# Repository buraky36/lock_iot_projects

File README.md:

# lock_iot_projects
Barfas Projects

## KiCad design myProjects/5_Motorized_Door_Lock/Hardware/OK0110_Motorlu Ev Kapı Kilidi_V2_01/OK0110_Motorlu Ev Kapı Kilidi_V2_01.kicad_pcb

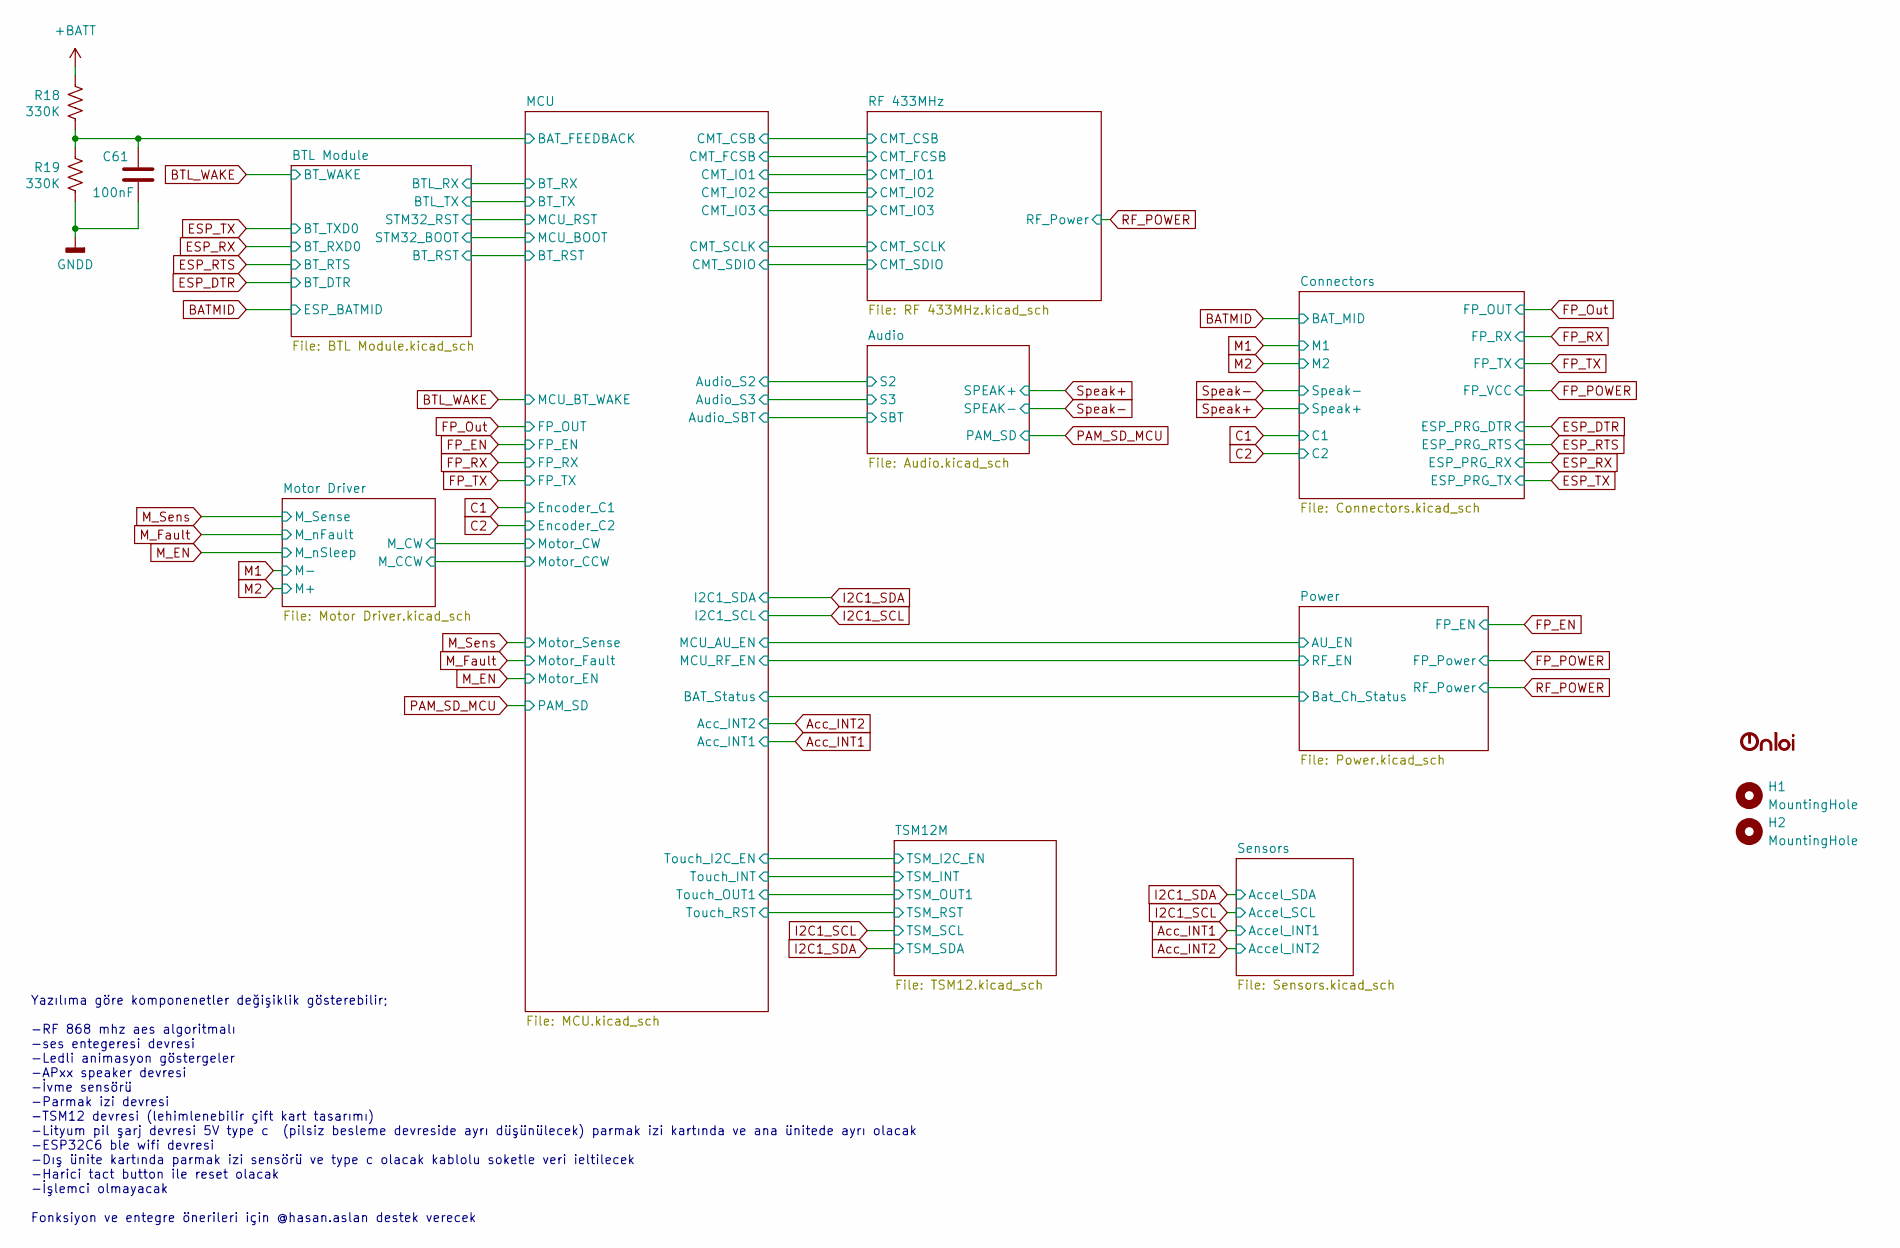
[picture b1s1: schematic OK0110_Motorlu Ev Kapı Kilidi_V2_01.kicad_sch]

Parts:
C61: 100nF; C_0402_1005Metric
H1, H2: MountingHole; MountingHole_4.3mm_M4
LOGO1: ONLOI_7_5x2_5mm
R18, R19: 330K; R_0402_1005Metric

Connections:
+BATT: R18.2; also elsewhere on the board
/MCU/BAT_FEEDBACK: C61.2, R18.1, R19.2; also elsewhere on the board
GNDD: C61.1, R19.1; also elsewhere on the board

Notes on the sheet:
Yazılıma göre komponenetler değişiklik gösterebilir; -RF 868 mhz aes algoritmalı -ses entegeresi devresi -Ledli animasyon göstergeler -APxx speaker devresi -İvme sensörü -Parmak izi devresi -TSM12 devresi (lehimlenebilir çift kart tasarımı) -Lityum pil şarj devresi 5V type c (pilsiz besleme devresi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

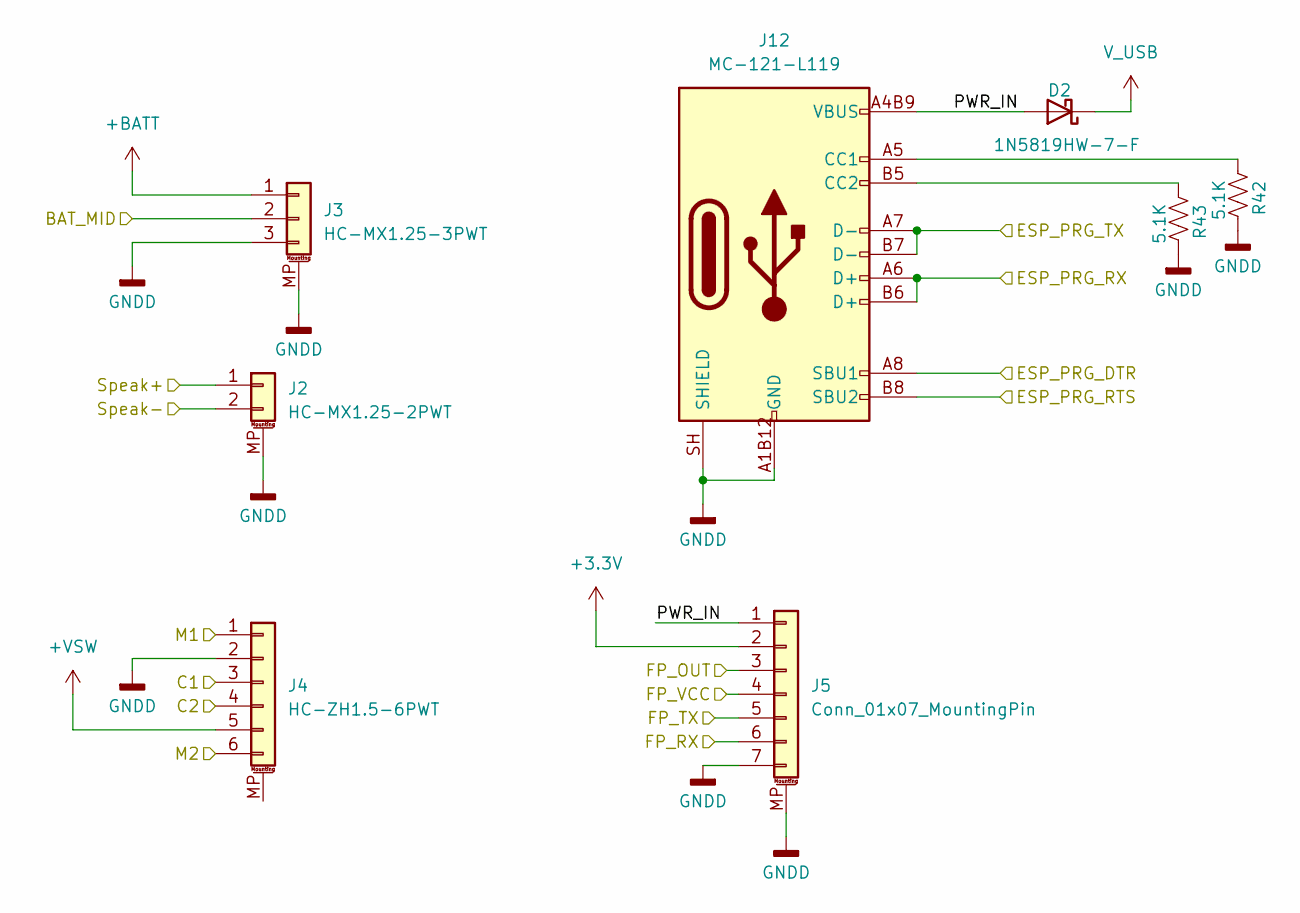
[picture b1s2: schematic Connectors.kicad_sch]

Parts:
D2: 1N5819HW-7-F; D_SOD-110
J2: HC-MX1.25-2PWT; JST_GH_SM02B-GHS-TB_1x02-1MP_P1.25mm_Horizontal
J3: HC-MX1.25-3PWT; JST_GH_SM03B-GHS-TB_1x03-1MP_P1.25mm_Horizontal
J4: HC-ZH1.5-6PWT; JST_ZE_SM06B-ZESS-TB_1x06-1MP_P1.50mm_Horizontal
J5: Conn_01x07_MountingPin; JST_SHL_SM07B-SHLS-TF_1x07-1MP_P1.00mm_Horizontal
J12: MC-121-L119; USB_C_Receptacle_GCT_USB4105-xx-A_16P_TopMnt_Horizontal
R42, R43: 5.1K; R_0402_1005Metric

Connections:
+3.3V: J5.2; also elsewhere on the board
+BATT: J3.1; also elsewhere on the board
+VSW: J4.5; also elsewhere on the board
/Connectors/PWR_IN: D2.2 (A), J5.1, J12.A4B9 (VBUS), J12.B4A9 (VBUS)
BATMID: J3.2; also elsewhere on the board
C1: J4.3; also elsewhere on the board
C2: J4.4; also elsewhere on the board
ESP_DTR: J12.A8 (SBU1); also elsewhere on the board
ESP_RTS: J12.B8 (SBU2); also elsewhere on the board
ESP_RX: J12.A6 (D+), J12.B6 (D+); also elsewhere on the board
ESP_TX: J12.A7 (D-), J12.B7 (D-); also elsewhere on the board
FP_Out: J5.3; also elsewhere on the board
FP_POWER: J5.4; also elsewhere on the board
FP_RX: J5.6; also elsewhere on the board
FP_TX: J5.5; also elsewhere on the board
GNDD: J2.MP (MountPin), J3.3, J3.MP (MountPin), J4.2, J5.7, J5.MP (MountPin), J12.A1B12 (GND), J12.B1A12 (GND), J12.SH (SHIELD), R42.2, R43.2; also elsewhere on the board
M1: J4.1; also elsewhere on the board
M2: J4.6; also elsewhere on the board
unnamed: J12.A5 (CC1), R42.1
unnamed: J12.B5 (CC2), R43.1
Speak+: J2.1; also elsewhere on the board
Speak-: J2.2; also elsewhere on the board
V_USB: D2.1 (K); also elsewhere on the board

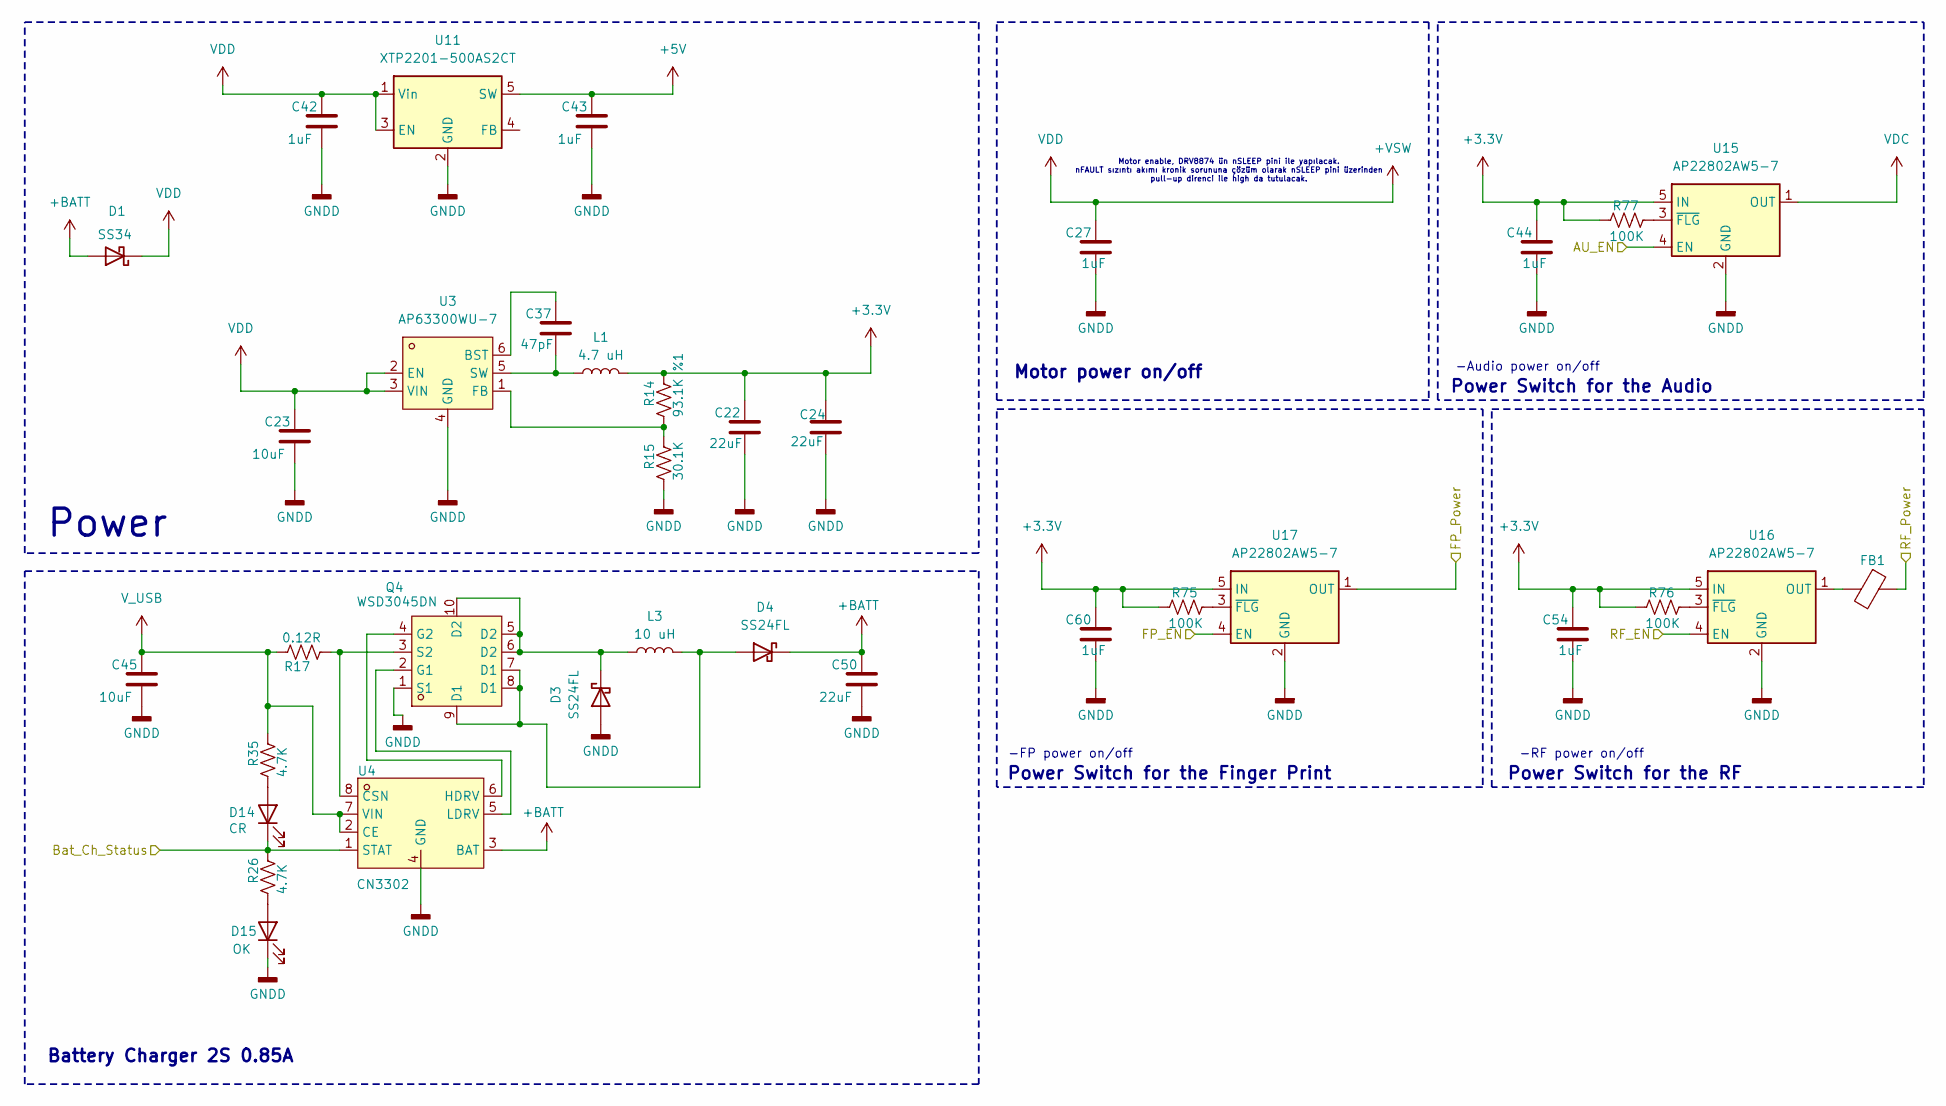
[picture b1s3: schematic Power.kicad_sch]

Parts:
C22, C24, C50: 22uF; C_0603_1608Metric
C23: 10uF; C_0402_1005Metric
C27, C42, C43, C44, C54, C60: 1uF; C_0402_1005Metric
C37: 47pF; C_0402_1005Metric
C45: 10uF; C_0603_1608Metric
D1: SS34; D_SMA
D3, D4: SS24FL; D_SOD-123F; MPN SS24FL
D14: CR; LED_0603_1608Metric
D15: OK; LED_0603_1608Metric
FB1: L_0805_2012Metric
L1: 4.7 uH; L_1008_2520Metric
L3: 10 uH; L_Cenker_CKCS6045
Q4: WSD3045DN; DFN-8_L3.2-W3.2-P0.65-LS3.4-BL-EP; MPN WSD3045DN33; LCSC Part C377868
R14: 93.1K %1; R_0402_1005Metric
R15: 30.1K; R_0402_1005Metric
R17: 0.12R; R_0603_1608Metric
R26, R35: 4.7K; R_0402_1005Metric
R75, R76, R77: 100K; R_0402_1005Metric
U3: AP63300WU-7; TSOT-23-6_L2.9-W1.6-P0.95-LS2.8-BR; MPN AP63300WU-7; LCSC Part C2158012
U4: CN3302; SOP-8_L4.9-W3.9-P1.27-LS6.0-BL; MPN CN3302; LCSC Part C559039
U11: XTP2201-500AS2CT; TSOT-23-5
U15, U16, U17: AP22802AW5-7; SOT-23-5

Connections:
+3.3V: C22.2, C24.1, C44.2, C54.2, C60.2, L1.2, R14.1, R75.1, R76.1, R77.1, U15.5 (IN), U16.5 (IN), U17.5 (IN); also elsewhere on the board
+5V: C43.2, U11.5 (SW); also elsewhere on the board
+BATT: C50.2, D1.2 (A), D4.1 (K), U4.3 (BAT); also elsewhere on the board
+VSW: C23.2, C27.2, C42.2, D1.1 (K), U3.2 (EN), U3.3 (VIN), U11.1 (Vin), U11.3 (EN); also elsewhere on the board
/MCU/BAT_Status: D14.1 (K), R26.1, U4.1 (STAT); also elsewhere on the board
/MCU/MCU_AU_EN: U15.4 (EN); also elsewhere on the board
/MCU/MCU_RF_EN: U16.4 (EN); also elsewhere on the board
FP_EN: U17.4 (EN); also elsewhere on the board
FP_POWER: U17.1 (OUT); also elsewhere on the board
GNDD: C22.1, C23.1, C24.2, C27.1, C42.1, C43.1, C44.1, C45.1, C50.1, C54.1, C60.1, D3.2 (A), D15.1 (K), Q4.1 (S1), R15.2, U3.4 (GND), U4.4 (GND), U11.2 (GND), U15.2 (GND), U16.2 (GND), U17.2 (GND); also elsewhere on the board
unnamed: D3.1 (K), L3.1, Q4.5 (D2), Q4.6 (D2), Q4.10 (D2)
unnamed: D4.2 (A), L3.2, Q4.7 (D1), Q4.8 (D1), Q4.9 (D1)
unnamed: D14.2 (A), R35.2
unnamed: D15.2 (A), R26.2
unnamed: Q4.2 (G1), U4.5 (LDRV)
unnamed: Q4.4 (G2), U4.6 (HDRV)
unnamed: Q4.3 (S2), R17.2, U4.8 (CSN)
unnamed: C37.2, U3.6 (BST)
unnamed: R14.2, R15.1, U3.1 (FB)
unnamed: C37.1, L1.1, U3.5 (SW)
unnamed: R77.2, U15.3 (~FLG)
unnamed: FB1.2, U16.1 (OUT)
unnamed: R76.2, U16.3 (~FLG)
unnamed: R75.2, U17.3 (~FLG)
RF_POWER: FB1.1; also elsewhere on the board
VDC: U15.1 (OUT); also elsewhere on the board
V_USB: C45.2, R17.1, R35.1, U4.2 (CE), U4.7 (VIN); also elsewhere on the board

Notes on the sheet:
-Audio power on/off
-RF power on/off
Battery Charger 2S 0.85A
Power Switch for the RF
Motor power on/off
Motor enable, DRV8874 ün nSLEEP pini ile yapılacak. nFAULT sızıntı akımı kronik sorununa çözüm olarak nSLEEP pini üzerinden pull-up direnci ile high da tutulacak.
Power Switch for the Audio
Power
Power Switch for the Finger Print
-FP power on/off

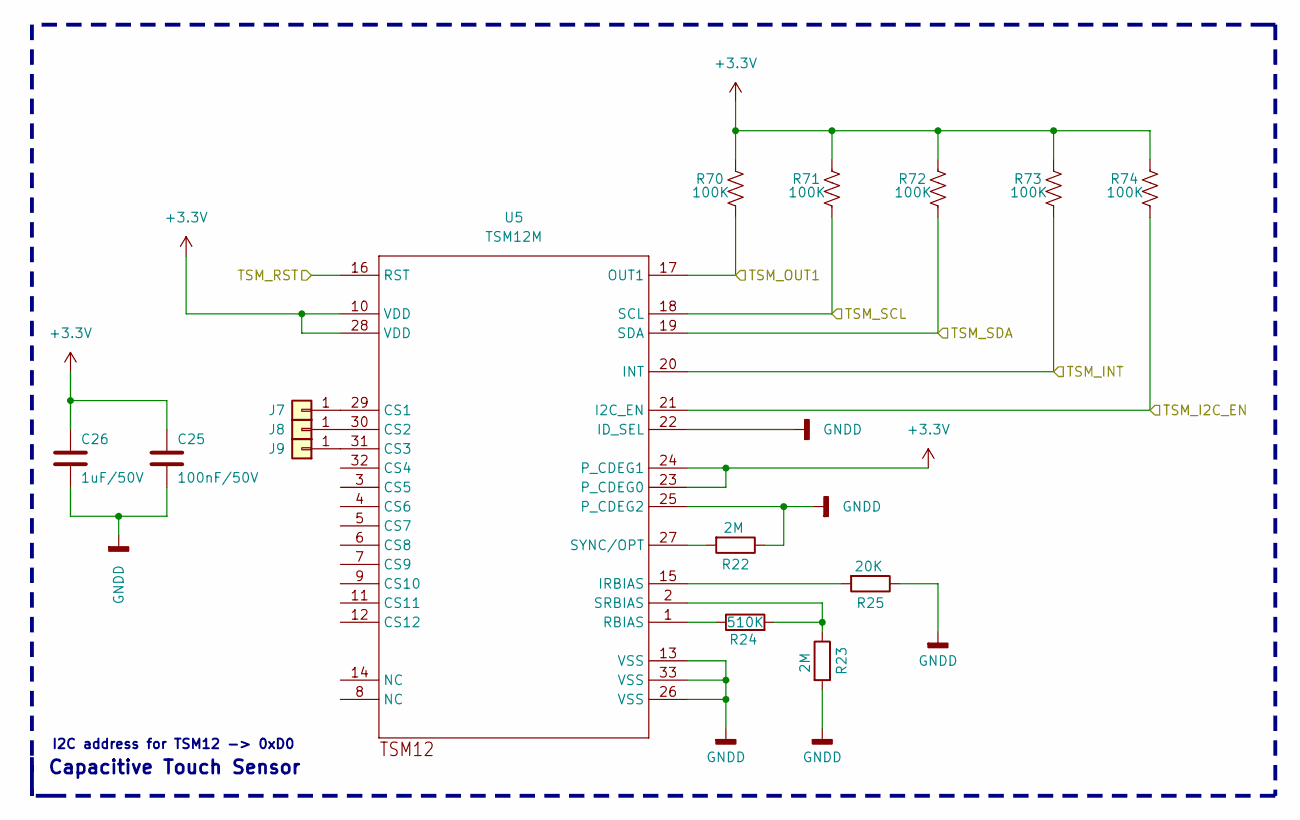
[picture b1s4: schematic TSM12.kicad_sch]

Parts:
C25: 100nF/50V; C_0402_1005Metric
C26: 1uF/50V; C_0402_1005Metric
J7, J8, J9: TestPoint:TestPoint_Keystone_5015_Micro_Mini; TestPoint_Keystone_5015_Micro_Mini
R22, R23: 2M; R_0402_1005Metric
R24: 510K; R_0402_1005Metric
R25: 20K; R_0402_1005Metric
R70, R71, R72, R73, R74: 100K; R_0402_1005Metric
U5: TSM12M; QFN-32-1EP_5x5mm_P0.5mm_EP3.1x3.1mm_ThermalVias

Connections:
+3.3V: C25.1, C26.1, R70.1, R71.1, R72.1, R73.1, R74.1, U5.10 (VDD), U5.23 (P_CDEG0), U5.24 (P_CDEG1), U5.28 (VDD); also elsewhere on the board
/MCU/Touch_I2C_EN: R74.2, U5.21 (I2C_EN); also elsewhere on the board
/MCU/Touch_INT: R73.2, U5.20 (INT); also elsewhere on the board
/MCU/Touch_OUT1: R70.2, U5.17 (OUT1); also elsewhere on the board
/MCU/Touch_RST: U5.16 (RST); also elsewhere on the board
GNDD: C25.2, C26.2, R22.1, R23.2, R25.1, U5.13 (VSS), U5.22 (ID_SEL), U5.25 (P_CDEG2), U5.26 (VSS), U5.33 (VSS); also elsewhere on the board
I2C1_SCL: R71.2, U5.18 (SCL); also elsewhere on the board
I2C1_SDA: R72.2, U5.19 (SDA); also elsewhere on the board
unnamed: J7.1 (Pin_1_1), U5.29 (CS1)
unnamed: J8.1 (Pin_1_1), U5.30 (CS2)
unnamed: J9.1 (Pin_1_1), U5.31 (CS3)
unnamed: R25.2, U5.15 (IRBIAS)
unnamed: R24.1, U5.1 (RBIAS)
unnamed: R23.1, R24.2, U5.2 (SRBIAS)
unnamed: R22.2, U5.27 (SYNC/OPT)

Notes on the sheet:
I2C address for TSM12 -> 0xD0
Capacitive Touch Sensor

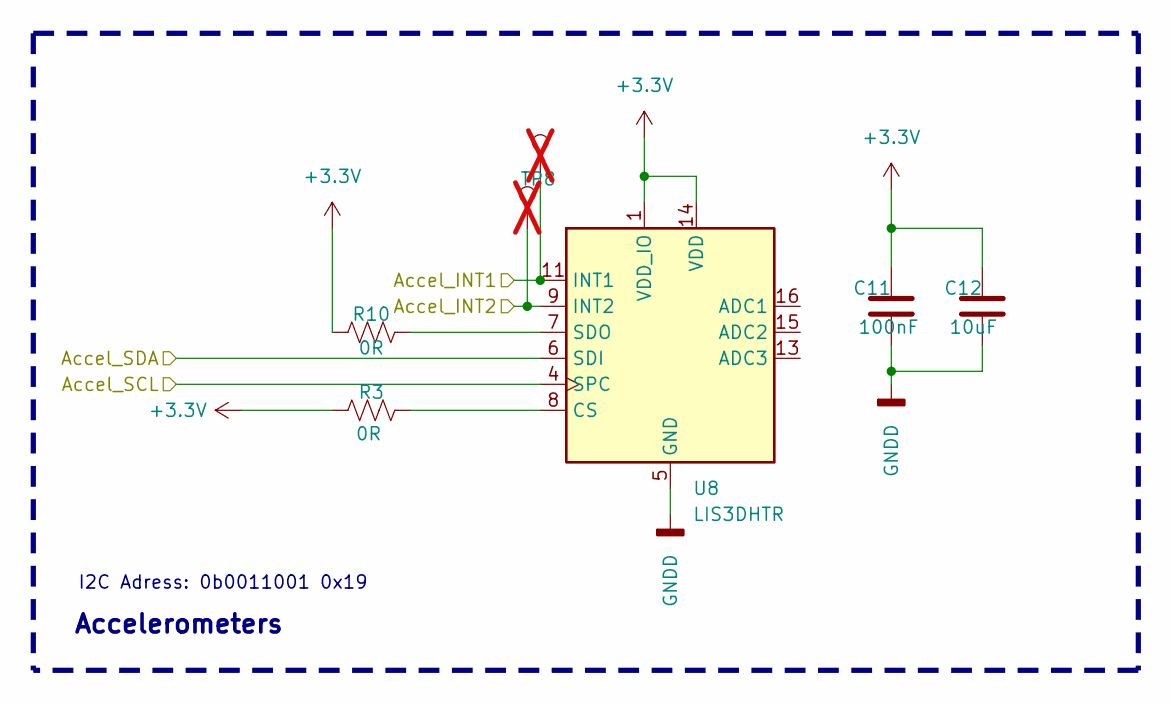
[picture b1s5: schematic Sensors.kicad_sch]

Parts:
C11: 100nF; C_0402_1005Metric
C12: 10uF; C_0402_1005Metric
R3, R10: 0R; R_0402_1005Metric
TP7, TP8: TestPoint; TestPoint_Pad_D1.0mm; not fitted
U8: LIS3DHTR; LGA-16_3x3mm_P0.5mm_LayoutBorder3x5y

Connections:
+3.3V: C11.1, C12.1, R3.1, R10.1, U8.1 (VDD_IO), U8.14 (VDD); also elsewhere on the board
Acc_INT1: TP7.1, U8.11 (INT1); also elsewhere on the board
Acc_INT2: TP8.1, U8.9 (INT2); also elsewhere on the board
GNDD: C11.2, C12.2, U8.5 (GND), U8.10 (GND), U8.12 (GND); also elsewhere on the board
I2C1_SCL: U8.4 (SPC); also elsewhere on the board
I2C1_SDA: U8.6 (SDI); also elsewhere on the board
unnamed: R3.2, U8.8 (CS)
unnamed: R10.2, U8.7 (SDO)

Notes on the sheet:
Accelerometers
I2C Adress: 0b0011001 0x19

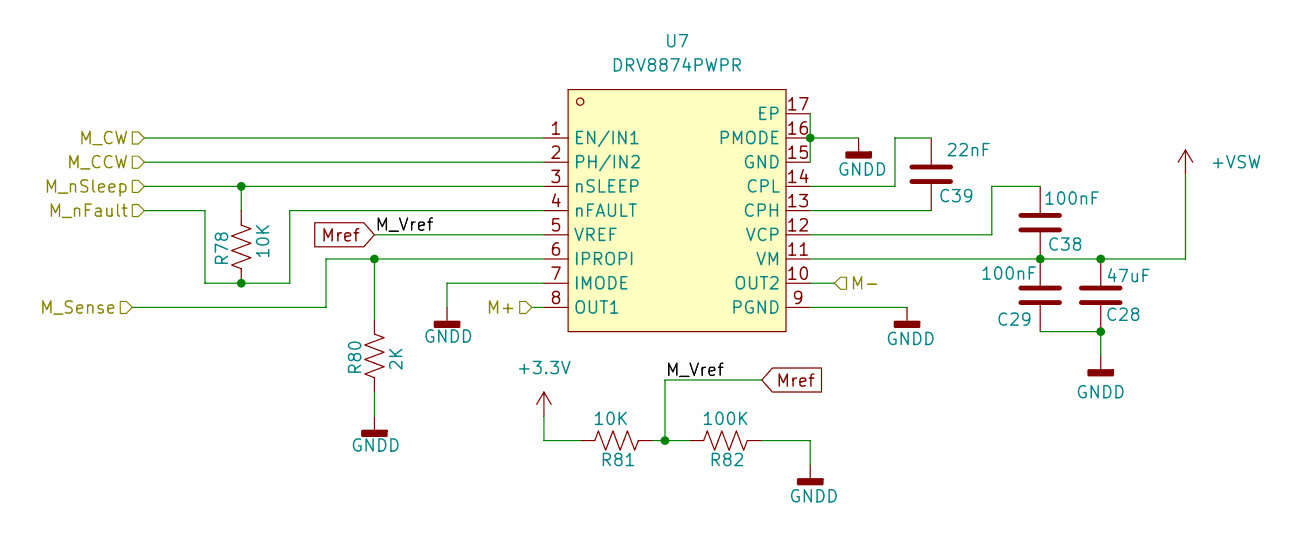
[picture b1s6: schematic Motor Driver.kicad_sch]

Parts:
C28: 47uF; C_1206_3216Metric
C29, C38: 100nF; C_0402_1005Metric
C39: 22nF; C_0402_1005Metric
R78, R81: 10K; R_0402_1005Metric
R80: 2K; R_0402_1005Metric
R82: 100K; R_0402_1005Metric
U7: DRV8874PWPR; HTSSOP-16_L5.0-W4.4-P0.65-LS6.4-BL-EP; MPN DRV8874PWPR; LCSC Part C1855818

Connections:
+3.3V: R81.2; also elsewhere on the board
+VSW: C28.2, C29.2, C38.1, U7.11 (VM); also elsewhere on the board
/MCU/Motor_CCW: U7.2 (PH/IN2); also elsewhere on the board
/MCU/Motor_CW: U7.1 (EN/IN1); also elsewhere on the board
GNDD: C28.1, C29.1, R80.1, R82.1, U7.7 (IMODE), U7.9 (PGND), U7.15 (GND), U7.16 (PMODE), U7.17 (EP); also elsewhere on the board
M1: U7.10 (OUT2); also elsewhere on the board
M2: U7.8 (OUT1); also elsewhere on the board
M_EN: R78.2, U7.3 (nSLEEP); also elsewhere on the board
M_Fault: R78.1, U7.4 (nFAULT); also elsewhere on the board
M_Sens: R80.2, U7.6 (IPROPI); also elsewhere on the board
Mref: R81.1, R82.2, U7.5 (VREF)
unnamed: C39.1, U7.13 (CPH)
unnamed: C39.2, U7.14 (CPL)
unnamed: C38.2, U7.12 (VCP)

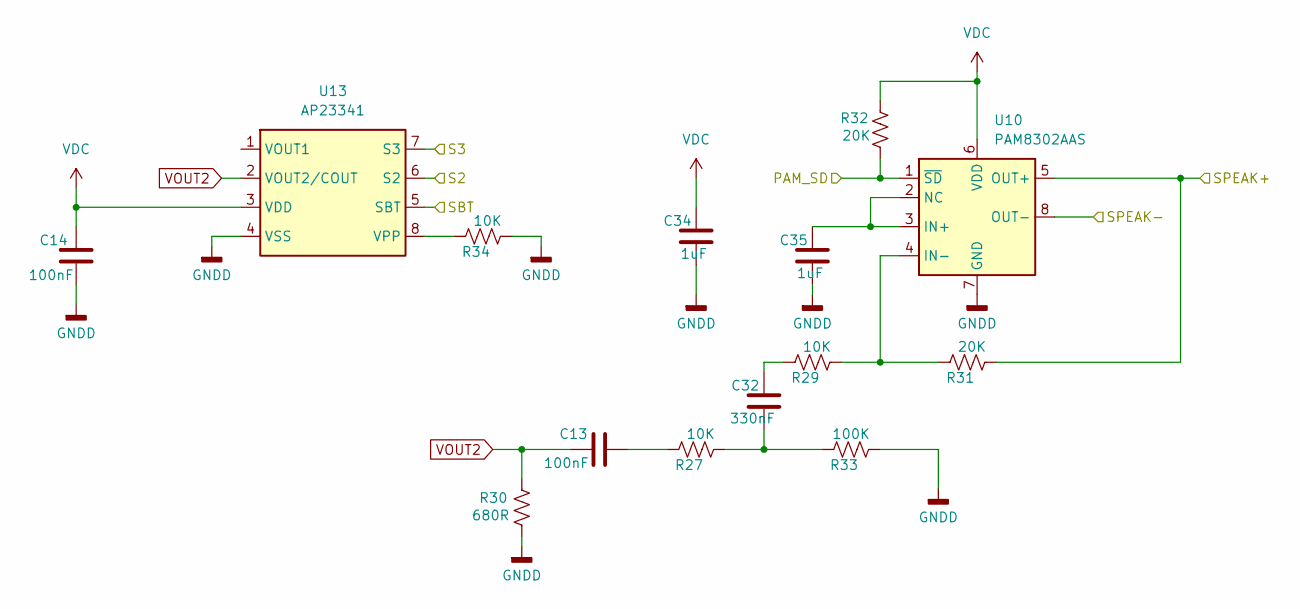
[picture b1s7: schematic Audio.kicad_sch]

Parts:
C13, C14: 100nF; C_0402_1005Metric
C32: 330nF; C_0402_1005Metric
C34, C35: 1uF; C_0402_1005Metric
R27, R29, R34: 10K; R_0402_1005Metric
R30: 680R; R_0402_1005Metric
R31, R32: 20K; R_0402_1005Metric
R33: 100K; R_0402_1005Metric
U10: PAM8302AAS; MSOP-8_3x3mm_P0.65mm
U13: AP23341; SOP-8_3.9x4.9mm_P1.27mm

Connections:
/Audio/S2: U13.6 (S2); also elsewhere on the board
/Audio/S3: U13.7 (S3); also elsewhere on the board
/Audio/SBT: U13.5 (SBT); also elsewhere on the board
GNDD: C14.1, C34.1, C35.1, R30.1, R33.2, R34.2, U10.7 (GND), U13.4 (VSS); also elsewhere on the board
unnamed: C13.1, R27.1
unnamed: C32.1, R27.2, R33.1
unnamed: C32.2, R29.1
unnamed: C35.2, U10.2 (NC), U10.3 (IN+)
unnamed: R29.2, R31.1, U10.4 (IN-)
unnamed: R34.1, U13.8 (VPP)
PAM_SD_MCU: R32.2, U10.1 (~SD); also elsewhere on the board
Speak+: R31.2, U10.5 (OUT+); also elsewhere on the board
Speak-: U10.8 (OUT-); also elsewhere on the board
VDC: C14.2, C34.2, R32.1, U10.6 (VDD), U13.3 (VDD); also elsewhere on the board
VOUT2: C13.2, R30.2, U13.2 (VOUT2/COUT)

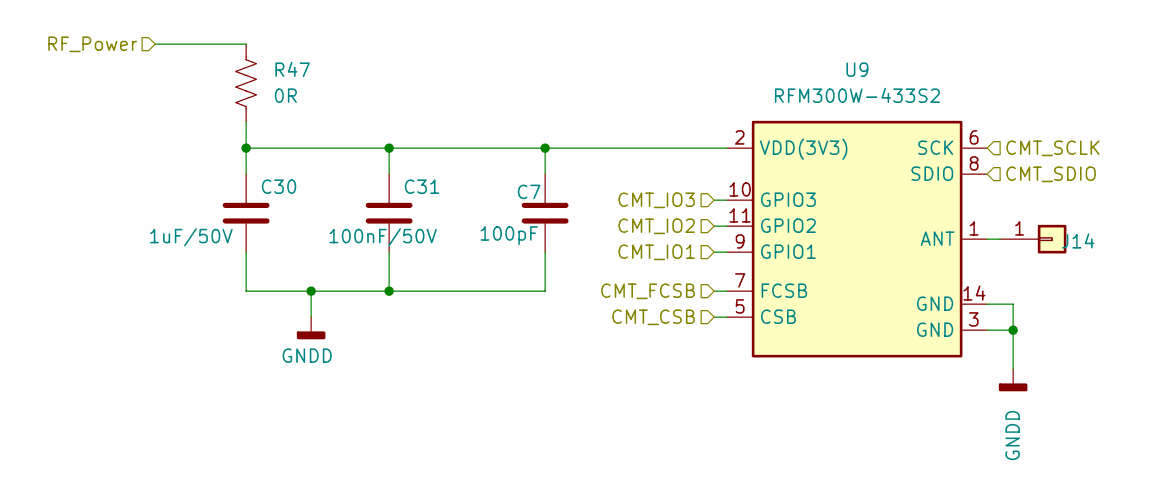
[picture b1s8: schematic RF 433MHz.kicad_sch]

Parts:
C7: 100pF; C_0402_1005Metric
C30: 1uF/50V; C_0402_1005Metric
C31: 100nF/50V; C_0402_1005Metric
J14: Conn_01x01; PinHeader_1x01_P2.54mm_Vertical
R47: 0R; R_0402_1005Metric
U9: RFM300W-433S2; HOPERF_RFM300

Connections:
/MCU/CMT_CSB: U9.5 (CSB); also elsewhere on the board
/MCU/CMT_FCSB: U9.7 (FCSB); also elsewhere on the board
/MCU/CMT_IO1: U9.9 (GPIO1); also elsewhere on the board
/MCU/CMT_IO2: U9.11 (GPIO2); also elsewhere on the board
/MCU/CMT_IO3: U9.10 (GPIO3); also elsewhere on the board
/MCU/CMT_SCLK: U9.6 (SCK); also elsewhere on the board
/MCU/CMT_SDIO: U9.8 (SDIO); also elsewhere on the board
GNDD: C7.1, C30.2, C31.2, U9.3 (GND), U9.14 (GND); also elsewhere on the board
unnamed: J14.1 (Pin_1_1), U9.1 (ANT)
unnamed: C7.2, C30.1, C31.1, R47.2, U9.2 (VDD(3V3))
RF_POWER: R47.1; also elsewhere on the board

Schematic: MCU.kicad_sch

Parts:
C9, C10: 100nF; C_0402_1005Metric
FID1, FID2, FID3, FID4: Fiducial; Fiducial_1mm_Mask3mm
J11: Conn_01x05; PinHeader_1x05_P2.00mm_Vertical
LED1, LED2, LED3: IN-PI22TAT5R5G5B; LED-SMD_4P-L2.7-W2.4-BR_TC2528RGB; MPN IN-PI22TAT5R5G5B; LCSC Part C22079459
R41: 100K; R_0402_1005Metric
R53: 500R; R_0402_1005Metric
SW1: SW_Push; SW_SPST_FSMSM
U2: STM32G070CBT6; LQFP-48_7x7mm_P0.5mm

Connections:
+3.3V: C9.2, J11.1, U2.4 (VBAT), U2.5 (VREF+), U2.6 (VDD); also elsewhere on the board
+5V: LED1.4 (VDD), LED2.4 (VDD), LED3.4 (VDD); also elsewhere on the board
/Audio/S2: U2.22 (PB10); also elsewhere on the board
/Audio/S3: U2.23 (PB11); also elsewhere on the board
/Audio/SBT: U2.24 (PB12); also elsewhere on the board
/BTL Module/BTL_RX: U2.13 (PA2); also elsewhere on the board
/BTL Module/BTL_TX: U2.14 (PA3); also elsewhere on the board
/MCU/BAT_FEEDBACK: U2.17 (PA6); also elsewhere on the board
/MCU/BAT_Status: U2.9 (PF1); also elsewhere on the board
/MCU/CMT_CSB: U2.15 (PA4); also elsewhere on the board
/MCU/CMT_FCSB: U2.16 (PA5); also elsewhere on the board
/MCU/CMT_IO1: U2.21 (PB2); also elsewhere on the board
/MCU/CMT_IO2: U2.19 (PB0); also elsewhere on the board
/MCU/CMT_IO3: U2.37 (PA15); also elsewhere on the board
/MCU/CMT_SCLK: U2.12 (PA1); also elsewhere on the board
/MCU/CMT_SDIO: U2.18 (PA7); also elsewhere on the board
/MCU/MCU_AU_EN: U2.8 (PF0); also elsewhere on the board
/MCU/MCU_RF_EN: U2.2 (PC14); also elsewhere on the board
/MCU/Motor_CCW: U2.38 (PD0); also elsewhere on the board
/MCU/Motor_CW: U2.41 (PD3); also elsewhere on the board
/MCU/Touch_I2C_EN: U2.45 (PB6); also elsewhere on the board
/MCU/Touch_INT: U2.46 (PB7); also elsewhere on the board
/MCU/Touch_OUT1: U2.44 (PB5); also elsewhere on the board
/MCU/Touch_RST: U2.43 (PB4); also elsewhere on the board
Acc_INT1: U2.3 (PC15); also elsewhere on the board
Acc_INT2: U2.39 (PD1); also elsewhere on the board
BTL_WAKE: U2.11 (PA0); also elsewhere on the board
C1: U2.30 (PC6); also elsewhere on the board
C2: U2.31 (PC7); also elsewhere on the board
ESP32_RST: U2.42 (PB3); also elsewhere on the board
FP_EN: U2.28 (PA8); also elsewhere on the board
FP_Out: R41.1, U2.1 (PC13); also elsewhere on the board
FP_RX: U2.29 (PA9/NC); also elsewhere on the board
FP_TX: U2.32 (PA10/NC); also elsewhere on the board
GNDD: C9.1, C10.1, J11.3, LED1.2 (VSS), LED2.2 (VSS), LED3.2 (VSS), R41.2, SW1.2, U2.7 (VSS); also elsewhere on the board
I2C1_SCL: U2.47 (PB8); also elsewhere on the board
I2C1_SDA: U2.48 (PB9); also elsewhere on the board
M_EN: U2.27 (PB15); also elsewhere on the board
M_Fault: U2.26 (PB14); also elsewhere on the board
M_Sens: U2.25 (PB13); also elsewhere on the board
NRST: C10.2, J11.2, SW1.1, U2.10 (NRST); also elsewhere on the board
unnamed: LED1.3 (DIN), R53.1
unnamed: LED1.1 (DOUT), LED2.3 (DIN)
unnamed: LED2.1 (DOUT), LED3.3 (DIN)
unnamed: R53.2, U2.20 (PB1)
PAM_SD_MCU: U2.34 (PA12/PA10); also elsewhere on the board
SWCLK: J11.4, U2.36 (PA14); also elsewhere on the board
SWDIO: J11.5, U2.35 (PA13)

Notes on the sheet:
RGB LED
MCU

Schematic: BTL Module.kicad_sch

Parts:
C17, C33, C62, C63: 100nF; C_0402_1005Metric
C36: 22uF/6.3V; C_0603_1608Metric
C40, C41: 12pF; C_0402_1005Metric
D5: LED_0603_1608Metric
J1: Conn_01x07; PinHeader_1x06_P1.27mm_Vertical
JP1: SolderJumper_2_Open; SolderJumper-2_P1.3mm_Open_Pad1.0x1.5mm
JP2: SolderJumper_2_Bridged; SolderJumper-2_P1.3mm_Bridged_Pad1.0x1.5mm
Q1: BC846BS; SOT-363_SC-70-6
R28, R36, R39, R61: 10K; R_0402_1005Metric
R37, R38: 12K; R_0402_1005Metric
R40: 680R; R_0402_1005Metric
R44, R45, R46, R48: 47R; R_0402_1005Metric
R49, R50, R51, R52: 330K; R_0402_1005Metric
SW2: SW_Push_SPST_NO_Alps_SKRK
U1: ESP32-C6-WROOM-1-N4; WIRELM-SMD_ESP32-C6-WROOM-1; MPN ESP32-C6-WROOM-1-N4; LCSC Part C6034714
X1: FL37S2-32.768-NLLLDTL; CRYSTAL-SMD_L7.0-W3.2-LS7.5; MPN FL37S2-32.768-NLLLDTL; LCSC Part C3034396

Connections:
+3.3V: C33.1, C36.1, R28.1; also elsewhere on the board
/BTL Module/<NO NET>: JP2.2 (B), R39.1, U1.7 (IO7)
/BTL Module/BTL_Power: J1.5, R37.1, R38.1, U1.2 (3V3)
/BTL Module/BTL_RX: U1.4 (IO4); also elsewhere on the board
/BTL Module/BTL_TX: U1.5 (IO5); also elsewhere on the board
BATMID: R49.2; also elsewhere on the board
BTL_WAKE: U1.27 (IO2); also elsewhere on the board
DTR: J1.2, Q1.1 (E1), R36.2, R45.2
ESP32_BOOT: JP1.2 (B), Q1.6 (C1), R37.2, U1.15 (IO9)
ESP32_RST: C17.1, Q1.3 (C2), R28.2, SW2.2, U1.3 (EN); also elsewhere on the board
ESP_BAT_MID: C62.2, R49.1, R50.2, U1.11 (IO10)
ESP_DTR: R45.1; also elsewhere on the board
ESP_RTS: R44.1; also elsewhere on the board
ESP_RX: R48.1; also elsewhere on the board
ESP_TX: R46.1; also elsewhere on the board
GNDD: C17.2, C33.2, C36.2, C40.2, C41.2, C62.1, C63.1, D5.1 (K), J1.6, JP1.1 (A), R39.2, R50.1, R52.1, SW2.1, U1.1 (GND), U1.28 (GND), U1.29 (GND), U1.30 (GND), U1.31 (GND), U1.32 (GND), U1.33 (GND), U1.34 (GND), U1.35 (GND), U1.36 (GND), U1.37 (GND); also elsewhere on the board
IO0: C40.1, U1.8 (IO0), X1.1
IO1: C41.1, U1.9 (IO1), X1.2 (GND)
IO8: R38.2, U1.10 (IO8)
NRST: U1.6 (IO6); also elsewhere on the board
unnamed: D5.2 (A), R40.1
unnamed: Q1.2 (B1), R61.2
unnamed: Q1.5 (B2), R36.1
unnamed: R40.2, U1.26 (IO3)
RTS: J1.1, Q1.4 (E2), R44.2, R61.1
RXD0: J1.3, R48.2, U1.24 (RXD0)
SWCLK: JP2.1 (A); also elsewhere on the board
TXD0: J1.4, R46.2, U1.25 (TXD0)
VUSB_DEDECT: C63.2, R51.1, R52.2, U1.12 (IO11)
V_USB: R51.2; also elsewhere on the board

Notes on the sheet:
ESP32-C6

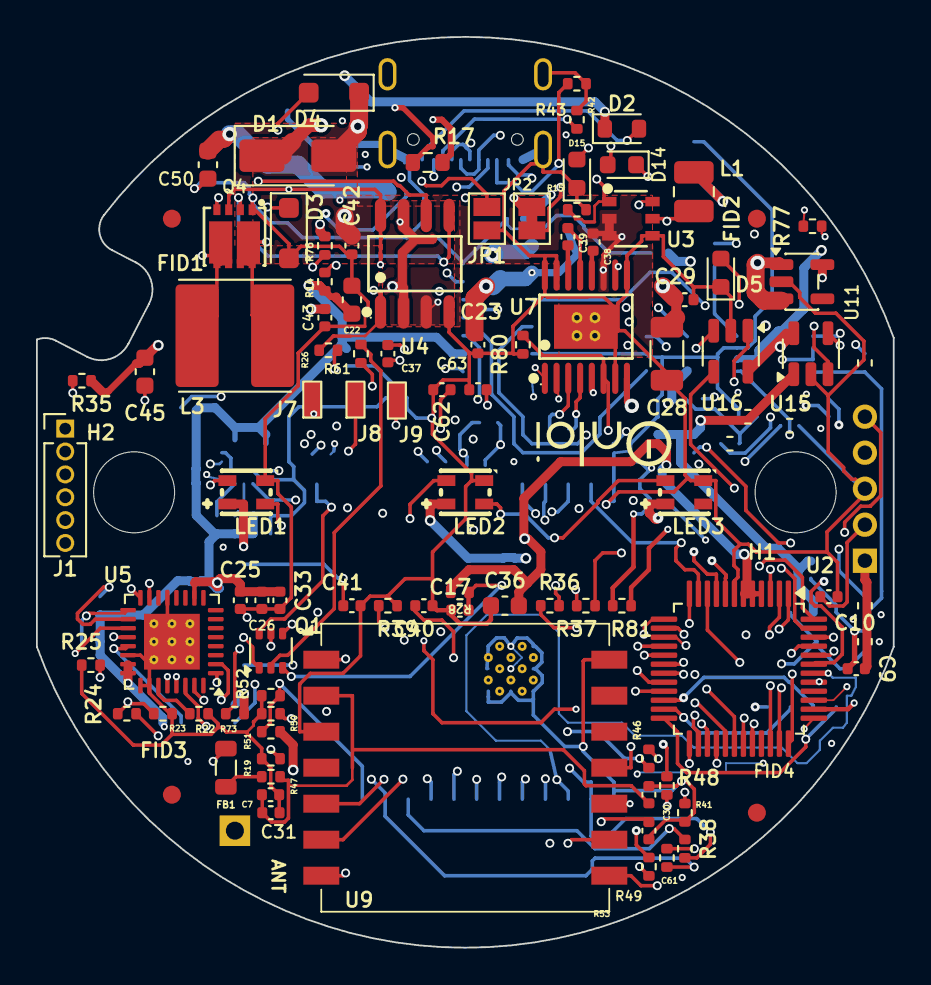
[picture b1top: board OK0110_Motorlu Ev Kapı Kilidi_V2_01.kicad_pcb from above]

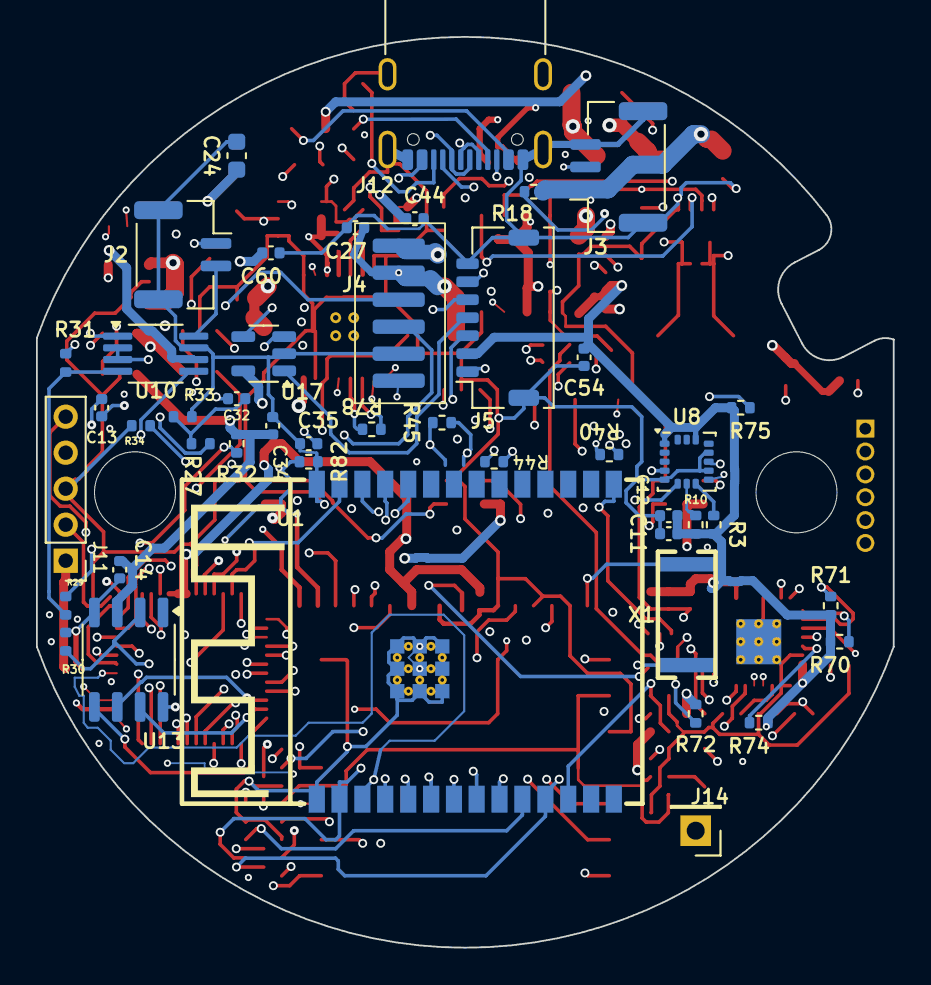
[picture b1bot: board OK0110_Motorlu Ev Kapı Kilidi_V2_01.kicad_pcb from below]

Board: 6 copper layers, 47.6 x 50.6 mm, 140 parts (45 on the bottom side), 118 nets.
